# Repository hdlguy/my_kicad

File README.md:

#               my_kicad

This is a repo to contain some simple attempts to use Kicad 6 to design printed circuit boards.

## File organization and version control

I like to make it so that design files are usable by just cloning them from GitHub but that is not completely possible with KiCad because libraries are external to the design folders and KiCad relies on user level pathname to access libraries.

Here are how I have my paths setup.

The official KiCad libraries are cloned from these url:

    https://gitlab.com/kicad/libraries/kicad-symbols
    https://gitlab.com/kicad/libraries/kicad-footprints
    https://gitlab.com/kicad/libraries/kicad-packages3d

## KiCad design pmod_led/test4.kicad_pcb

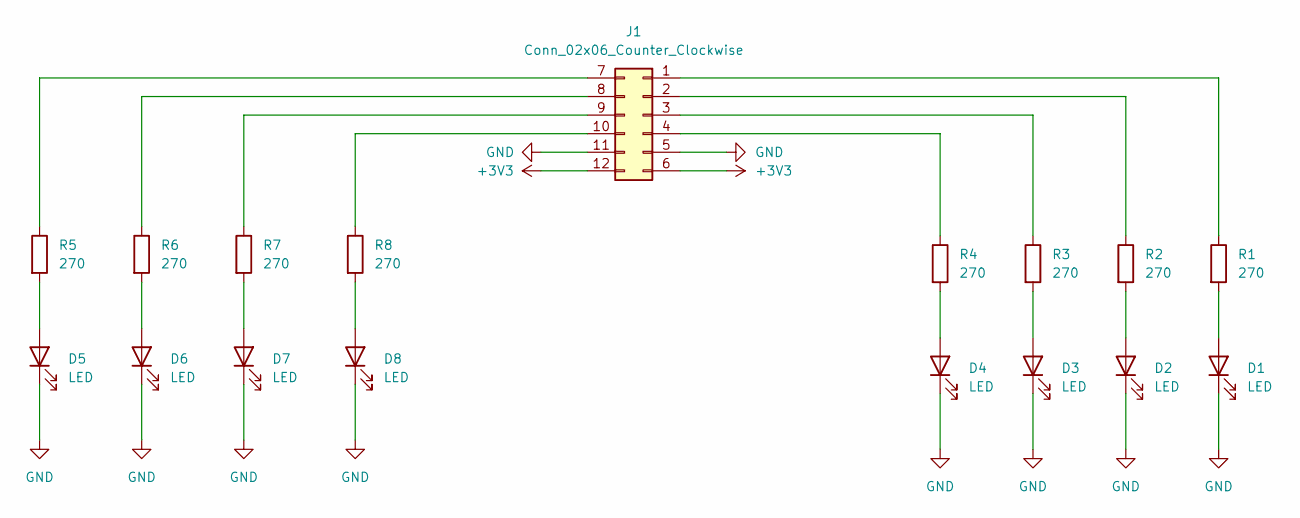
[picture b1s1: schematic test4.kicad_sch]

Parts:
D1, D2, D3, D4, D5, D6, D7, D8: LED; LED_0603_1608Metric
J1: Conn_02x06_Counter_Clockwise; PinHeader_2x06_P2.54mm_Horizontal
R1, R2, R3, R4, R5, R6, R7, R8: 270; R_0603_1608Metric

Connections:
+3V3: J1.6, J1.12
GND: D1.1 (K), D2.1 (K), D3.1 (K), D4.1 (K), D5.1 (K), D6.1 (K), D7.1 (K), D8.1 (K), J1.5, J1.11
unnamed: D6.2 (A), R6.2
unnamed: D7.2 (A), R7.2
unnamed: D8.2 (A), R8.2
unnamed: D4.2 (A), R4.2
unnamed: D3.2 (A), R3.2
unnamed: D2.2 (A), R2.2
unnamed: D1.2 (A), R1.2
unnamed: J1.1, R1.1
unnamed: J1.2, R2.1
unnamed: J1.3, R3.1
unnamed: J1.4, R4.1
unnamed: J1.8, R6.1
unnamed: J1.9, R7.1
unnamed: J1.10, R8.1
unnamed: J1.7, R5.1
unnamed: D5.2 (A), R5.2

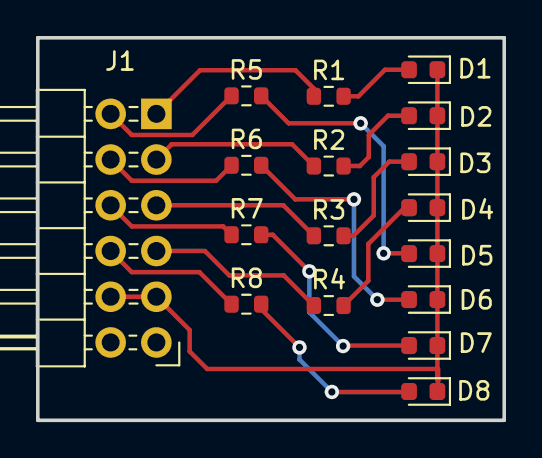
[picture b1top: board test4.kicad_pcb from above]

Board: 2 copper layers, 25.9 x 21.2 mm, 17 parts (0 on the bottom side), 18 nets.

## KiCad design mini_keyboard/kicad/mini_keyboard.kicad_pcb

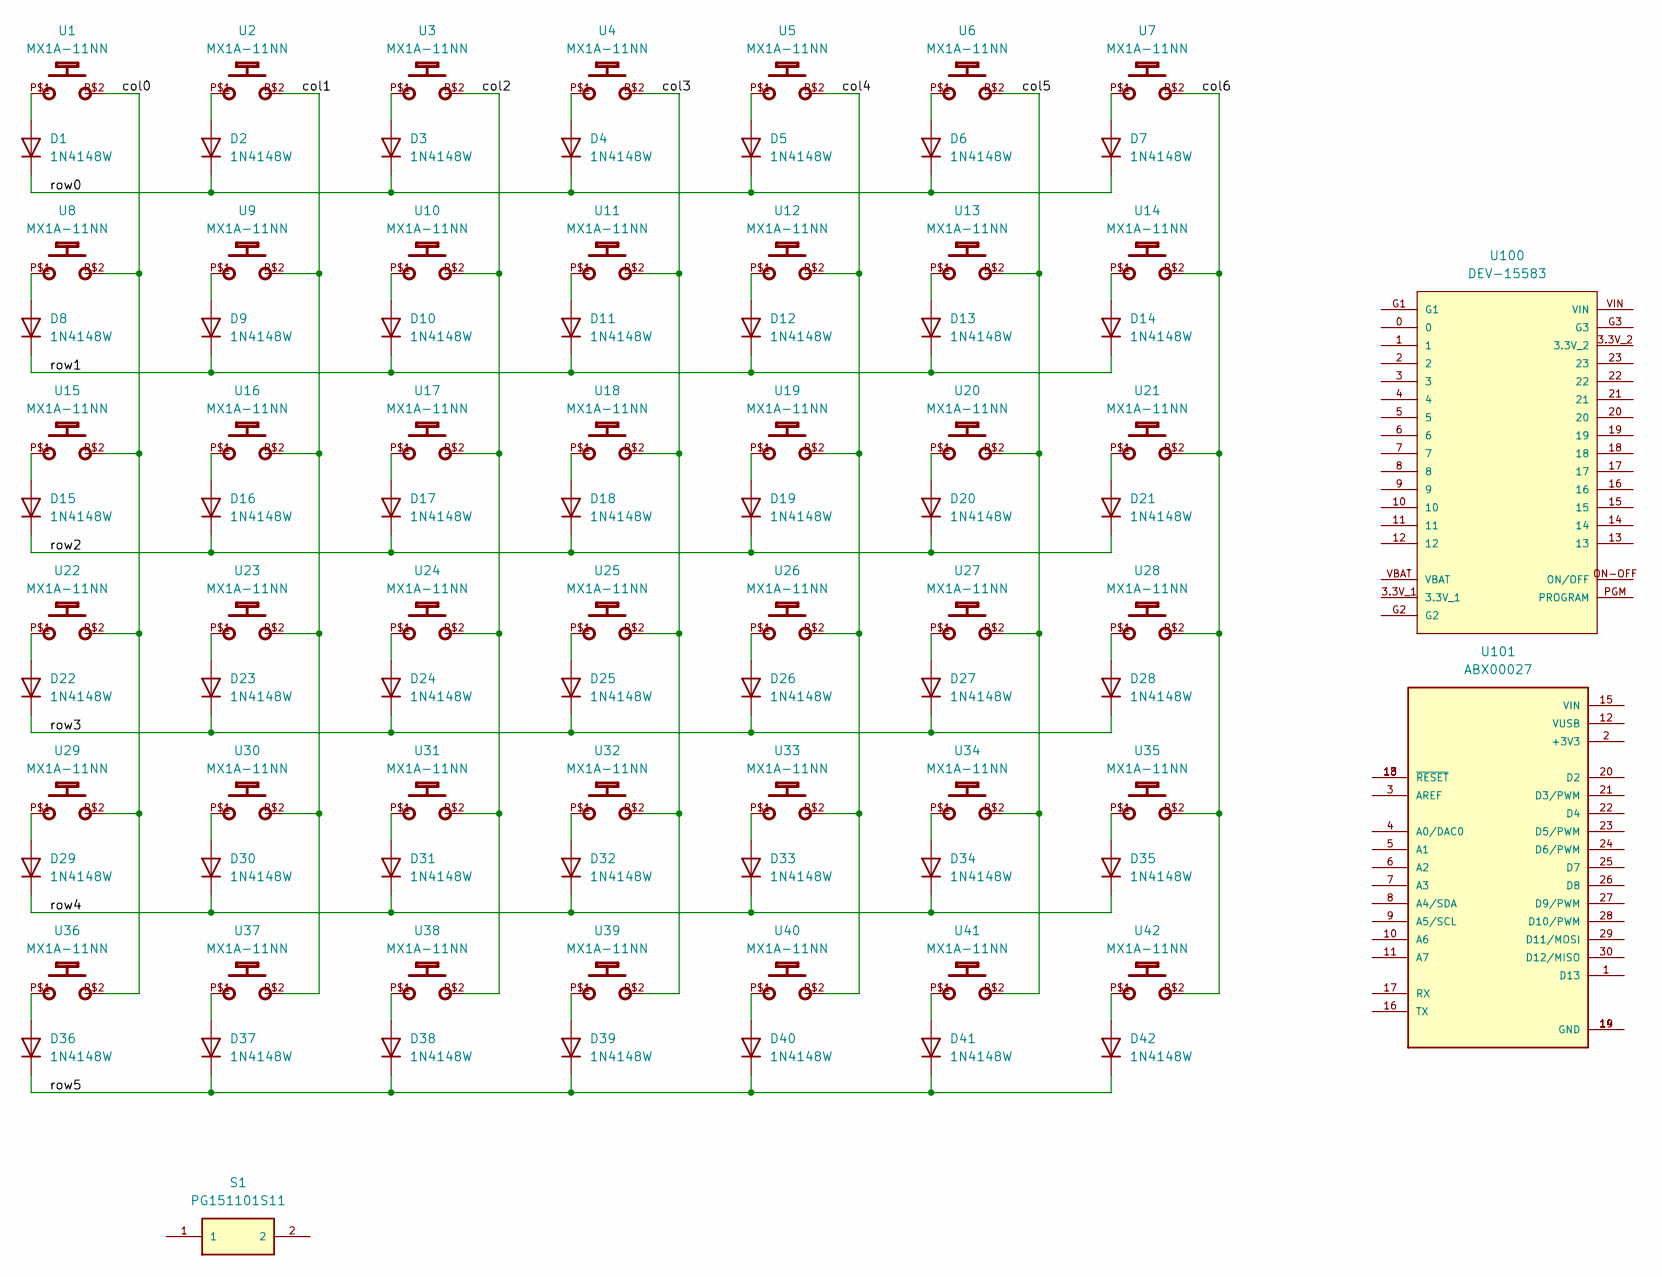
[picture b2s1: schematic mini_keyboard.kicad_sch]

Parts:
D1, D2, D3, D4, D5, D6, D7, D8, D9, D10, D11, D12, D13, D14, D15, D16, D17, D18, D19, D20, D21, D22, D23, D24, D25, D26, D27, D28, D29, D30, D31, D32, D33, D34, D35, D36, D37, D38, D39, D40, D41, D42: 1N4148W; D_SOD-123
S1: PG151101S11; SW_PG151101S11; PARTREV A
U1, U2, U3, U4, U5, U6, U7, U8, U9, U10, U11, U12, U13, U14, U15, U16, U17, U18, U19, U20, U21, U22, U23, U24, U25, U26, U27, U28, U29, U30, U31, U32, U33, U34, U35, U36, U37, U38, U39, U40, U41, U42: MX1A-11NN; CHERRY_MX1A-11NN_SWITCH
U100: DEV-15583; MODULE_DEV-15583
U101: ABX00027; MODULE_ABX00027

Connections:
/col0: U1.P$2, U8.P$2, U15.P$2, U22.P$2, U29.P$2, U36.P$2
/col1: U2.P$2, U9.P$2, U16.P$2, U23.P$2, U30.P$2, U37.P$2
/col2: U3.P$2, U10.P$2, U17.P$2, U24.P$2, U31.P$2, U38.P$2
/col3: U4.P$2, U11.P$2, U18.P$2, U25.P$2, U32.P$2, U39.P$2
/col4: U5.P$2, U12.P$2, U19.P$2, U26.P$2, U33.P$2, U40.P$2
/col5: U6.P$2, U13.P$2, U20.P$2, U27.P$2, U34.P$2, U41.P$2
/col6: U7.P$2, U14.P$2, U21.P$2, U28.P$2, U35.P$2, U42.P$2
/row0: D1.1 (K), D2.1 (K), D3.1 (K), D4.1 (K), D5.1 (K), D6.1 (K), D7.1 (K)
/row1: D8.1 (K), D9.1 (K), D10.1 (K), D11.1 (K), D12.1 (K), D13.1 (K), D14.1 (K)
/row2: D15.1 (K), D16.1 (K), D17.1 (K), D18.1 (K), D19.1 (K), D20.1 (K), D21.1 (K)
/row3: D22.1 (K), D23.1 (K), D24.1 (K), D25.1 (K), D26.1 (K), D27.1 (K), D28.1 (K)
/row4: D29.1 (K), D30.1 (K), D31.1 (K), D32.1 (K), D33.1 (K), D34.1 (K), D35.1 (K)
/row5: D36.1 (K), D37.1 (K), D38.1 (K), D39.1 (K), D40.1 (K), D41.1 (K), D42.1 (K)
unnamed: D1.2 (A), U1.P$1
unnamed: D2.2 (A), U2.P$1
unnamed: D3.2 (A), U3.P$1
unnamed: D4.2 (A), U4.P$1
unnamed: D5.2 (A), U5.P$1
unnamed: D6.2 (A), U6.P$1
unnamed: D7.2 (A), U7.P$1
unnamed: D8.2 (A), U8.P$1
unnamed: D9.2 (A), U9.P$1
unnamed: D10.2 (A), U10.P$1
unnamed: D11.2 (A), U11.P$1
unnamed: D12.2 (A), U12.P$1
unnamed: D13.2 (A), U13.P$1
unnamed: D14.2 (A), U14.P$1
unnamed: D15.2 (A), U15.P$1
unnamed: D16.2 (A), U16.P$1
unnamed: D17.2 (A), U17.P$1
unnamed: D18.2 (A), U18.P$1
unnamed: D19.2 (A), U19.P$1
unnamed: D20.2 (A), U20.P$1
unnamed: D21.2 (A), U21.P$1
unnamed: D22.2 (A), U22.P$1
unnamed: D23.2 (A), U23.P$1
unnamed: D24.2 (A), U24.P$1
unnamed: D25.2 (A), U25.P$1
unnamed: D26.2 (A), U26.P$1
unnamed: D27.2 (A), U27.P$1
unnamed: D28.2 (A), U28.P$1
unnamed: D29.2 (A), U29.P$1
unnamed: D30.2 (A), U30.P$1
unnamed: D31.2 (A), U31.P$1
unnamed: D32.2 (A), U32.P$1
unnamed: D33.2 (A), U33.P$1
unnamed: D34.2 (A), U34.P$1
unnamed: D35.2 (A), U35.P$1
unnamed: D36.2 (A), U36.P$1
unnamed: D37.2 (A), U37.P$1
unnamed: D38.2 (A), U38.P$1
unnamed: D39.2 (A), U39.P$1
unnamed: D40.2 (A), U40.P$1
unnamed: D41.2 (A), U41.P$1
unnamed: D42.2 (A), U42.P$1
unnamed: U101.14 (GND), U101.19 (GND)
unnamed: U101.13 (~RESET), U101.18 (~RESET)

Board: 2 copper layers, 87 parts (45 on the bottom side), 57 nets, no tracks yet.

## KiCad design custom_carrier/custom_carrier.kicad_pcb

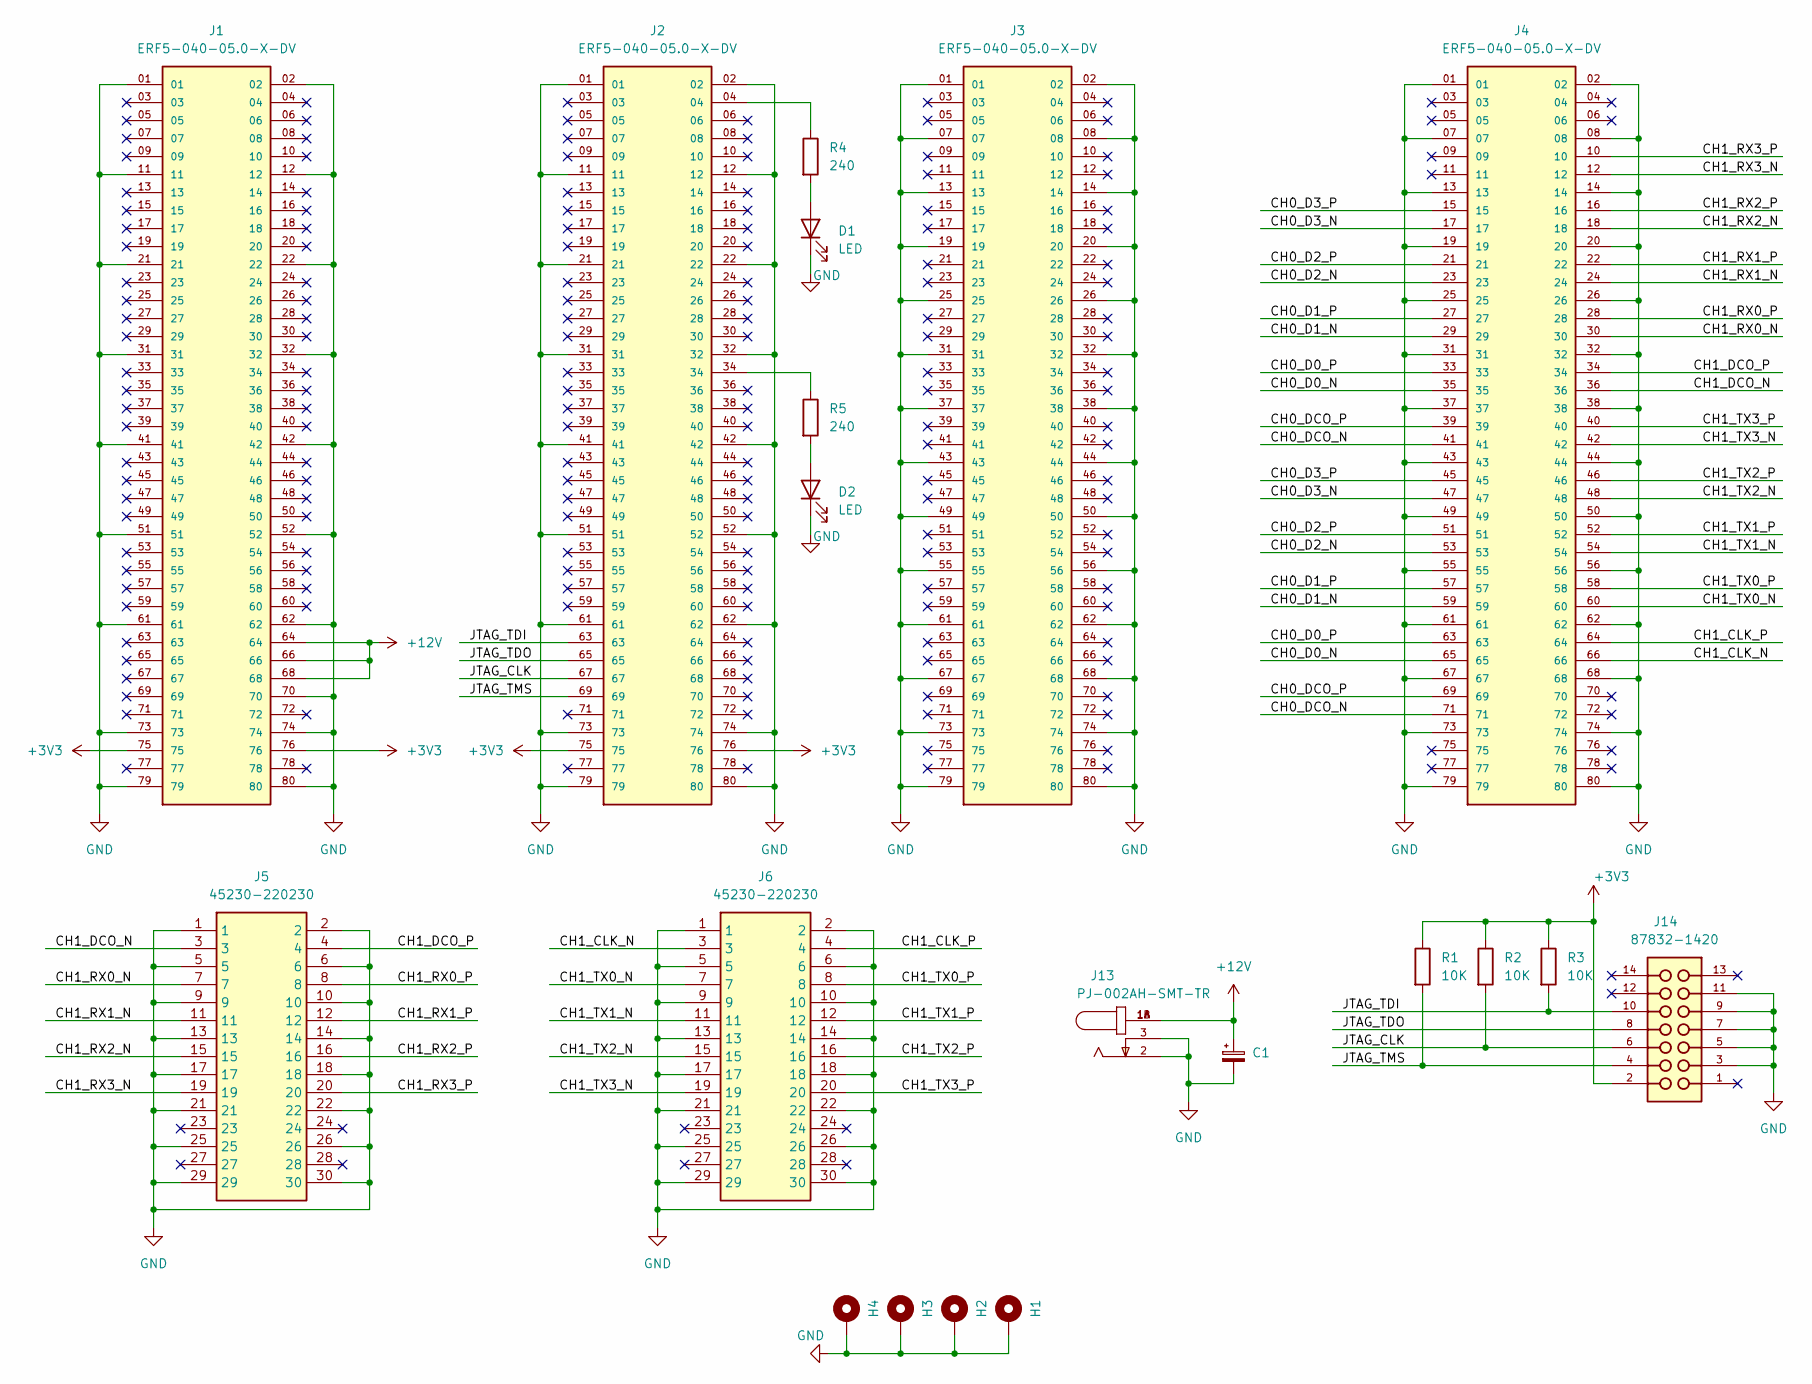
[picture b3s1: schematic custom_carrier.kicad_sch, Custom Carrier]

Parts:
C1: 22UF/25V; CP_EIA-3528-15_AVX-H; partnumber TCJB226M025R0150
D1, D2: LED; LED_0603_1608Metric
H1, H2, H3, H4: standoff_hole; MountingHole_2.2mm_M2_DIN965_Pad
J1, J2, J3, J4: ERF5-040-05.0-X-DV; SAMTEC_ERF5-040-05.0-X-DV; PARTREV F
J5, J6: 45230-220230; 45230220230; Manufacturer_Part_Number 45230-220230; Mouser Part Number 517-45230-220230
J13: PJ-002AH-SMT-TR; CUI_PJ-002AH-SMT-TR
J14: 87832-1420; MOLEX_87832-1420
R1, R2, R3: 10K; R_0603_1608Metric
R4, R5: 240; R_0603_1608Metric

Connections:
+3V3: J1.75, J1.76, J2.75, J2.76, J14.2, R1.1, R2.1, R3.1
+12V: C1.1, J1.64, J1.66, J1.68, J13.1A, J13.1B
/CH0_D0_N: J4.35, J4.65
/CH0_D0_P: J4.33, J4.63
/CH0_D1_N: J4.29, J4.59
/CH0_D1_P: J4.27, J4.57
/CH0_D2_N: J4.23, J4.53
/CH0_D2_P: J4.21, J4.51
/CH0_D3_N: J4.17, J4.47
/CH0_D3_P: J4.15, J4.45
/CH0_DCO_N: J4.41, J4.71
/CH0_DCO_P: J4.39, J4.69
/CH1_CLK_N: J4.66, J6.3
/CH1_CLK_P: J4.64, J6.4
/CH1_DCO_N: J4.36, J5.3
/CH1_DCO_P: J4.34, J5.4
/CH1_RX0_N: J4.30, J5.7
/CH1_RX0_P: J4.28, J5.8
/CH1_RX1_N: J4.24, J5.11
/CH1_RX1_P: J4.22, J5.12
/CH1_RX2_N: J4.18, J5.15
/CH1_RX2_P: J4.16, J5.16
/CH1_RX3_N: J4.12, J5.19
/CH1_RX3_P: J4.10, J5.20
/CH1_TX0_N: J4.60, J6.7
/CH1_TX0_P: J4.58, J6.8
/CH1_TX1_N: J4.54, J6.11
/CH1_TX1_P: J4.52, J6.12
/CH1_TX2_N: J4.48, J6.15
/CH1_TX2_P: J4.46, J6.16
/CH1_TX3_N: J4.42, J6.19
/CH1_TX3_P: J4.40, J6.20
/JTAG_CLK: J2.67, J14.6, R2.2
/JTAG_TDI: J2.63, J14.10, R3.2
/JTAG_TDO: J2.65, J14.8
/JTAG_TMS: J2.69, J14.4, R1.2
GND: C1.2, D1.1 (K), D2.1 (K), H1.1, H2.1, H3.1, H4.1, J1.01, J1.02, J1.11, J1.12, J1.21, J1.22, J1.31, J1.32, J1.41, J1.42, J1.51, J1.52, J1.61, J1.62, J1.70, J1.73, J1.74, J1.79, J1.80, J2.01, J2.02, J2.11, J2.12, J2.21, J2.22, J2.31, J2.32, J2.41, J2.42, J2.51, J2.52, J2.61, J2.62, J2.73, J2.74, J2.79, J2.80, J3.01, J3.02, J3.07, J3.08, J3.13, J3.14, J3.19, J3.20, J3.25, J3.26, J3.31, J3.32, J3.37, J3.38, J3.43, J3.44, J3.49, J3.50, J3.55, J3.56, J3.61, J3.62, J3.67, J3.68, J3.73, J3.74, J3.79, J3.80, J4.01, J4.02, J4.07, J4.08, J4.13, J4.14, J4.19, J4.20, J4.25, J4.26, J4.31, J4.32, J4.37, J4.38, J4.43, J4.44, J4.49, J4.50, J4.55, J4.56, J4.61, J4.62, J4.67, J4.68, J4.73, J4.74, J4.79, J4.80, J5.1, J5.2, J5.5, J5.6, J5.9, J5.10, J5.13, J5.14, J5.17, J5.18, J5.21, J5.22, J5.25, J5.26, J5.29, J5.30, J6.1, J6.2, J6.5, J6.6, J6.9, J6.10, J6.13, J6.14, J6.17, J6.18, J6.21, J6.22, J6.25, J6.26, J6.29, J6.30, J13.2, J13.3, J14.3, J14.5, J14.7, J14.9, J14.11
unnamed: D1.2 (A), R4.2
unnamed: D2.2 (A), R5.2
unnamed: J2.04, R4.1
unnamed: J2.34, R5.1

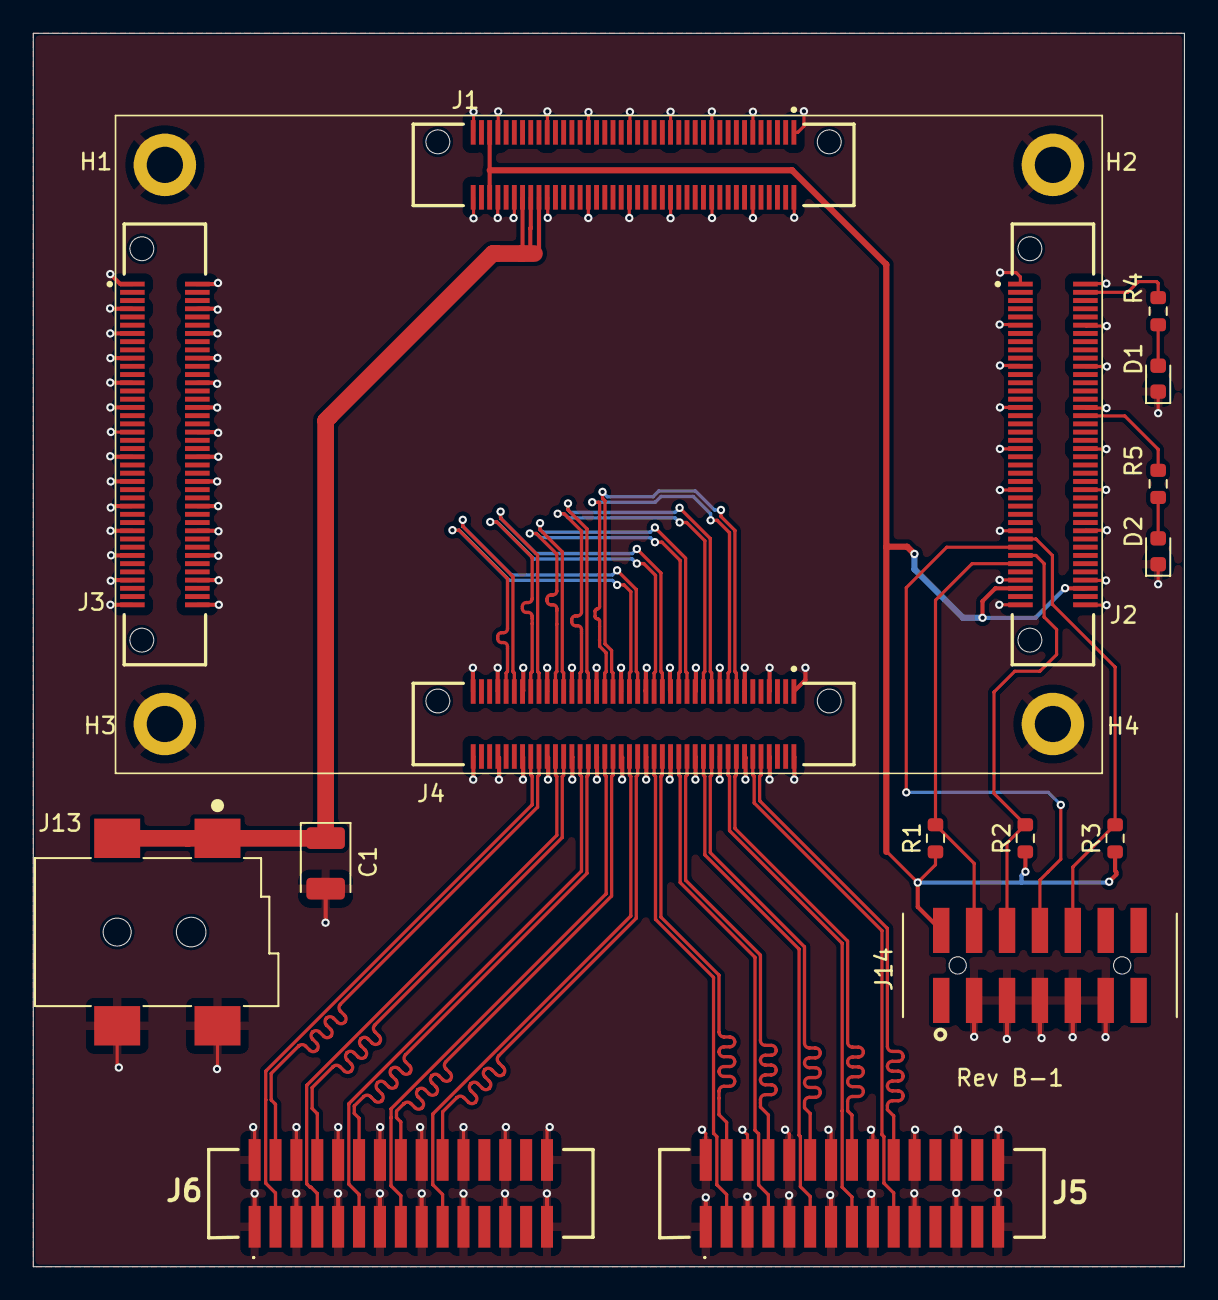
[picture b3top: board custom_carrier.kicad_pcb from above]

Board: 4 copper layers, 70.0 x 75.0 mm, 20 parts (0 on the bottom side), 41 nets.

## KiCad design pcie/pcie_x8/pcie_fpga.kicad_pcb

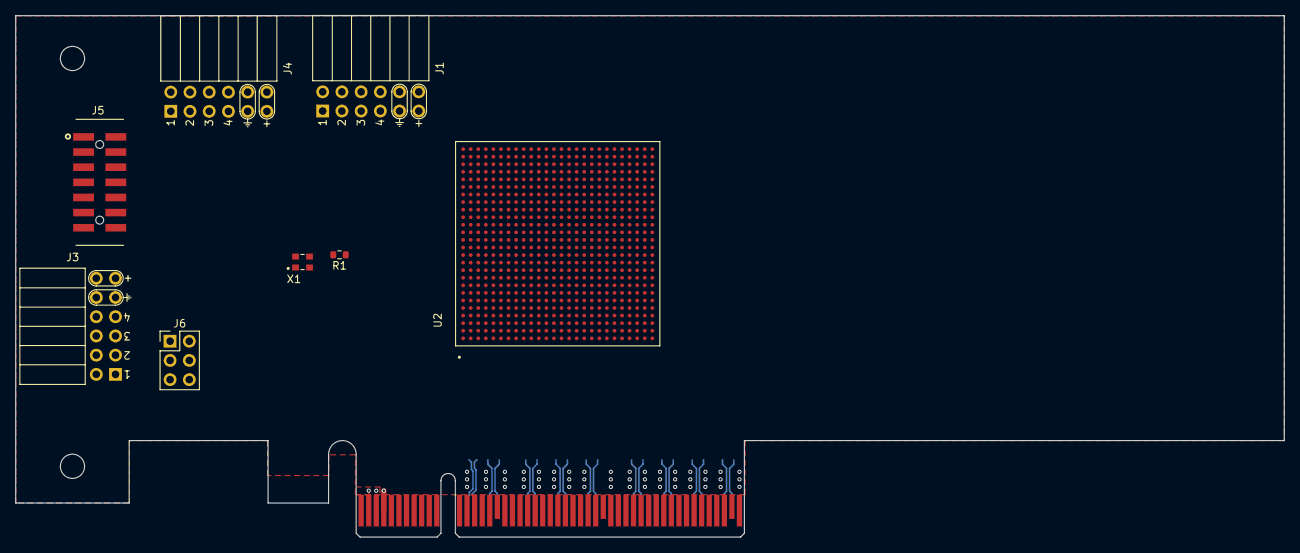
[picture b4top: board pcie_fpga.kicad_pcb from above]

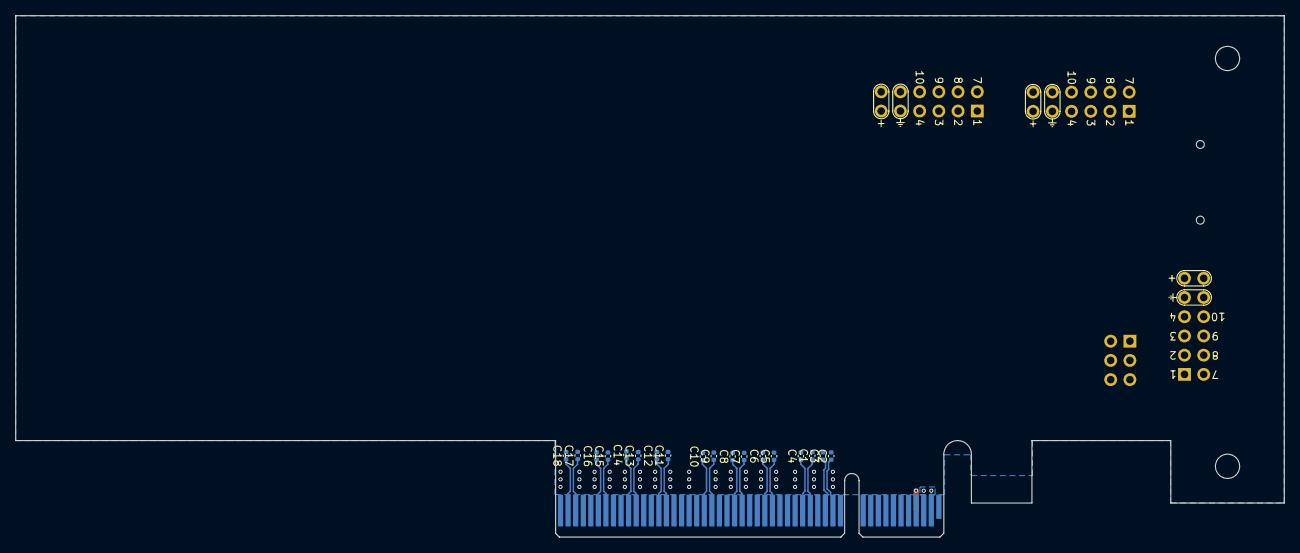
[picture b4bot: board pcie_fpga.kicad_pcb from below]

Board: 6 copper layers, 167.7 x 68.9 mm, 27 parts (18 on the bottom side), 77 nets.

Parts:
C1, C2, C3, C4, C5, C6, C7, C8, C9, C10, C11, C12, C13, C14, C15, C16, C17, C18: 0.01uf; C_0402_1005Metric
J1, J3, J4: PMOD_Host_Conn_02x06; PMOD_PinSocket_2x06_P2.54mm_Horizontal
J2: PCIexpress_x8
J5: 87832-1420; MOLEX_87832-1420
J6: Conn_02x03_Odd_Even; PinHeader_2x03_P2.54mm_Vertical
R1: 10; R_0603_1608Metric
U2: XCAU10P-1FFVB676I; IC_XCAU10P-1FFVB676I
X1: ECS-2520MVQ-1000-BN-TR; OSC_ECS-2520S25-250-FN-TR

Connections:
+3V3: J2.A9 (+3.3V), J2.A10 (+3.3V), J2.B8 (+3.3V), X1.4 (VDD)
+12V: J2.A2 (+12V), J2.A3 (+12V), J2.B1 (+12V), J2.B2 (+12V), J2.B3 (+12V)
/ac_refclk_N: C3.2, U2.V6 (MGTREFCLK0N_225)
/ac_refclk_P: C2.2, U2.V7 (MGTREFCLK0P_225)
/oscout: R1.2, X1.3 (OUT)
/per0_N: C4.1, J2.A17 (PERn0)
/per0_P: C1.1, J2.A16 (PERp0)
/per1_N: C6.1, J2.A22 (PERn1)
/per1_P: C5.1, J2.A21 (PERp1)
/per2_N: C8.1, J2.A26 (PERn2)
/per2_P: C7.1, J2.A25 (PERp2)
/per3_N: C10.1, J2.A30 (PERn3)
/per3_P: C9.1, J2.A29 (PERp3)
/per4_N: C12.1, J2.A36 (PERn4)
/per4_P: C11.1, J2.A35 (PERp4)
/per5_N: C14.1, J2.A40 (PERn5)
/per5_P: C13.1, J2.A39 (PERp5)
/per6_N: C16.1, J2.A44 (PERn6)
/per6_P: C15.1, J2.A43 (PERp6)
/per7_N: C18.1, J2.A48 (PERn7)
/per7_P: C17.1, J2.A47 (PERp7)
/pet0_N: J2.B15 (PETn0), U2.P1 (MGTHRXN3_225)
/pet0_P: J2.B14 (PETp0), U2.P2 (MGTHRXP3_225)
/pet1_N: J2.B20 (PETn1), U2.T1 (MGTHRXN2_225)
/pet1_P: J2.B19 (PETp1), U2.T2 (MGTHRXP2_225)
/pet2_N: J2.B24 (PETn2), U2.V1 (MGTHRXN1_225)
/pet2_P: J2.B23 (PETp2), U2.V2 (MGTHRXP1_225)
/pet3_N: J2.B28 (PETn3), U2.Y1 (MGTHRXN0_225)
/pet3_P: J2.B27 (PETp3), U2.Y2 (MGTHRXP0_225)
/pet4_N: J2.B34 (PETn4), U2.AB1 (MGTHRXN3_224)
/pet4_P: J2.B33 (PETp4), U2.AB2 (MGTHRXP3_224)
/pet5_N: J2.B38 (PETn5), U2.AD1 (MGTHRXN2_224)
/pet5_P: J2.B37 (PETp5), U2.AD2 (MGTHRXP2_224)
/pet6_N: J2.B42 (PETn6), U2.AE3 (MGTHRXN1_224)
/pet6_P: J2.B41 (PETp6), U2.AE4 (MGTHRXP1_224)
/pet7_N: J2.B46 (PETn7), U2.AF1 (MGTHRXN0_224)
/pet7_P: J2.B45 (PETp7), U2.AF2 (MGTHRXP0_224)
/pre_per0_N: C4.2, U2.R4 (MGTHTXN3_225)
/pre_per0_P: C1.2, U2.R5 (MGTHTXP3_225)
/pre_per1_N: C6.2, U2.U4 (MGTHTXN2_225)
/pre_per1_P: C5.2, U2.U5 (MGTHTXP2_225)
/pre_per2_N: C8.2, U2.W4 (MGTHTXN1_225)
/pre_per2_P: C7.2, U2.W5 (MGTHTXP1_225)
/pre_per3_N: C10.2, U2.AA4 (MGTHTXN0_225)
/pre_per3_P: C9.2, U2.AA5 (MGTHTXP0_225)
/pre_per4_N: C12.2, U2.AC4 (MGTHTXN3_224)
/pre_per4_P: C11.2, U2.AC5 (MGTHTXP3_224)
/pre_per5_N: C14.2, U2.AD6 (MGTHTXN2_224)
/pre_per5_P: C13.2, U2.AD7 (MGTHTXP2_224)
/pre_per6_N: C16.2, U2.AE8 (MGTHTXN1_224)
/pre_per6_P: C15.2, U2.AE9 (MGTHTXP1_224)
/pre_per7_N: C18.2, U2.AF6 (MGTHTXN0_224)
/pre_per7_P: C17.2, U2.AF7 (MGTHTXP0_224)
/prsnt_x1: J2.B17 (~PRSNT2), J6.1
/prsnt_x4: J2.B31 (~PRSNT2), J6.3
/prsnt_x8: J2.B48 (~PRSNT2), J6.5
/prsntn: J2.A1 (~PRSNT1), J6.2, J6.4, J6.6
/refclk_N: C3.1, J2.A14 (REFCLK-)
/refclk_P: C2.1, J2.A13 (REFCLK+)
GND: J2.A4 (GND), J2.A12 (GND), J2.A15 (GND), J2.A18 (GND), J2.A20 (GND), J2.A23 (GND), J2.A24 (GND), J2.A27 (GND), J2.A28 (GND), J2.A31 (GND), J2.A34 (GND), J2.A37 (GND), J2.A38 (GND), J2.A41 (GND), J2.A42 (GND), J2.A45 (GND), J2.A46 (GND), J2.A49 (GND), J2.B4 (GND), J2.B7 (GND), J2.B13 (GND), J2.B16 (GND), J2.B18 (GND), J2.B21 (GND), J2.B22 (GND), J2.B25 (GND), J2.B26 (GND), J2.B29 (GND), J2.B32 (GND), J2.B35 (GND), J2.B36 (GND), J2.B39 (GND), J2.B40 (GND), J2.B43 (GND), J2.B44 (GND), J2.B47 (GND), J2.B49 (GND), U2.A1 (GND_1), U2.A2 (GND_1), U2.A5 (GND_1), U2.A6 (GND_1), U2.A8 (GND_1), U2.A11 (GND_1), U2.A16 (GND_1), U2.A21 (GND_1), U2.A26 (GND_1), U2.AA1 (GND_1), U2.AA2 (GND_1), U2.AA3 (GND_1), U2.AA6 (GND_2), U2.AA8 (GND_2), U2.AA16 (GND_2), U2.AA26 (GND_2), U2.AB3 (GND_2), U2.AB4 (GND_2), U2.AB8 (GND_2), U2.AB13 (GND_2), U2.AB23 (GND_2), U2.AC1 (GND_2), U2.AC2 (GND_2), U2.AC3 (GND_2), U2.AC6 (GND_3), U2.AC8 (GND_3), U2.AC9 (GND_3), U2.AC10 (GND_3), U2.AC20 (GND_3), U2.AC25 (GND_3), U2.AD3 (GND_3), U2.AD4 (GND_3), U2.AD5 (GND_3), U2.AD10 (GND_3), U2.AD17 (GND_3), U2.AE1 (GND_3), U2.AE2 (GND_4), U2.AE5 (GND_4), U2.AE6 (GND_4), U2.AE10 (GND_4), U2.AE14 (GND_4), U2.AE19 (GND_4), U2.AE24 (GND_4), U2.AF3 (GND_4), U2.AF4 (GND_4), U2.AF5 (GND_4), U2.AF8 (GND_4), U2.AF9 (GND_4), U2.AF10 (GND_5), U2.AF11 (GND_5), U2.AF16 (GND_5), U2.AF21 (GND_5), U2.AF26 (GND_5), U2.B3 (GND_5), U2.B4 (GND_5), U2.B5 (GND_5), U2.B8 (GND_5), U2.B13 (GND_5), U2.B18 (GND_5), U2.B23 (GND_5), U2.C1 (GND_6), U2.C2 (GND_6), U2.C5 (GND_6), U2.C6 (GND_6), U2.C8 (GND_6), U2.C10 (GND_6), U2.C15 (GND_6), U2.C25 (GND_6), U2.D3 (GND_6), U2.D4 (GND_6), U2.D5 (GND_6), U2.D8 (GND_6), U2.D12 (GND_7), U2.D22 (GND_7), U2.E1 (GND_7), U2.E2 (GND_7), U2.E3 (GND_7), U2.E6 (GND_7), U2.E8 (GND_7), U2.E19 (GND_7), U2.F3 (GND_7), U2.F4 (GND_7), U2.F8 (GND_7), U2.F11 (GND_7), U2.F16 (GND_8), U2.F21 (GND_8), U2.F26 (GND_8), U2.G1 (GND_8), U2.G2 (GND_8), U2.G3 (GND_8), U2.G6 (GND_8), U2.G8 (GND_8), U2.G13 (GND_8), U2.G23 (GND_8), U2.H3 (GND_8), U2.H4 (GND_8), U2.H8 (GND_9), U2.H20 (GND_9), U2.J1 (GND_9), U2.J2 (GND_9), U2.J3 (GND_9), U2.J6 (GND_9), U2.J8 (GND_9), U2.J17 (GND_9), U2.K3 (GND_9), U2.K4 (GND_9), U2.K8 (GND_9), U2.K12 (GND_9), U2.K14 (GND_10), U2.K16 (GND_10), U2.K19 (GND_10), U2.K24 (GND_10), U2.L1 (GND_10), U2.L2 (GND_10), U2.L3 (GND_10), U2.L6 (GND_10), U2.L8 (GND_10), U2.L11 (GND_10), U2.L13 (GND_10), U2.L15 (GND_10), U2.L17 (GND_11), U2.L21 (GND_11), U2.L26 (GND_11), U2.M3 (GND_11), U2.M4 (GND_11), U2.M8 (GND_11), U2.M10 (GND_11), U2.M12 (GND_11), U2.M14 (GND_11), U2.M16 (GND_11), U2.M23 (GND_11), U2.N1 (GND_11), U2.N2 (GND_12), U2.N3 (GND_12), U2.N6 (GND_12), U2.N8 (GND_12), U2.N11 (GND_12), U2.N15 (GND_12), U2.N17 (GND_12), U2.N20 (GND_12), U2.N25 (GND_12), U2.P3 (GND_12), U2.P4 (GND_12), U2.P8 (GND_12), U2.P10 (GND_12), U2.P12 (GND_13), U2.P16 (GND_13), U2.R1 (GND_13), U2.R2 (GND_13), U2.R3 (GND_13), U2.R6 (GND_13), U2.R8 (GND_13), U2.R11 (GND_13), U2.R15 (GND_13), U2.R17 (GND_13), U2.R19 (GND_13), U2.R24 (GND_13), U2.T3 (GND_14), U2.T4 (GND_14), U2.T8 (GND_14), U2.T10 (GND_14), U2.T12 (GND_14), U2.T16 (GND_14), U2.T21 (GND_14), U2.T26 (GND_14), U2.U1 (GND_14), U2.U2 (GND_14), U2.U3 (GND_14), U2.U6 (GND_14), U2.U8 (GND_15), U2.U11 (GND_15), U2.U13 (GND_15), U2.U15 (GND_15), U2.U17 (GND_15), U2.U18 (GND_15), U2.V3 (GND_15), U2.V4 (GND_15), U2.V8 (GND_15), U2.V10 (GND_15), U2.V12 (GND_15), U2.V14 (GND_15), U2.V16 (GND_16), U2.V20 (GND_16), U2.V25 (GND_16), U2.W1 (GND_16), U2.W2 (GND_16), U2.W3 (GND_16), U2.W6 (GND_16), U2.W8 (GND_16), U2.W17 (GND_16), U2.W22 (GND_16), U2.Y3 (GND_16), U2.Y4 (GND_16), U2.Y8 (GND_16), U2.Y19 (GND_16), X1.2 (GND)
unnamed: U2.A7 (MGTAVTT_R), U2.AB5 (MGTAVTT_R), U2.AE7 (MGTAVTT_R), U2.C7 (MGTAVTT_R), U2.E7 (MGTAVTT_R), U2.F5 (MGTAVTT_R), U2.G7 (MGTAVTT_R), U2.H5 (MGTAVTT_R), U2.K5 (MGTAVTT_R), U2.M5 (MGTAVTT_R), U2.P5 (MGTAVTT_R), U2.T5 (MGTAVTT_R), U2.V5 (MGTAVTT_R), U2.Y5 (MGTAVTT_R)
unnamed: U2.AA7 (MGTAVCC_R), U2.AC7 (MGTAVCC_R), U2.J7 (MGTAVCC_R), U2.L7 (MGTAVCC_R), U2.N7 (MGTAVCC_R), U2.W7 (MGTAVCC_R)
unnamed: U2.AA11 (VCCO_0), U2.AD12 (VCCO_0)
unnamed: U2.AA21 (VCCO_64), U2.AB18 (VCCO_64), U2.AD22 (VCCO_64)
unnamed: U2.AC15 (VCCO_84), U2.Y14 (VCCO_84)
unnamed: U2.E9 (VCCO_85), U2.H10 (VCCO_85)
unnamed: U2.E14 (VCCO_86), U2.H15 (VCCO_86)
unnamed: U2.E24 (VCCO_66), U2.H25 (VCCO_66), U2.J22 (VCCO_66)
unnamed: U2.K11 (VCCINT_1), U2.K13 (VCCINT_1), U2.K15 (VCCINT_1), U2.K17 (VCCINT_1), U2.L10 (VCCINT_1), U2.L12 (VCCINT_1), U2.L14 (VCCINT_1), U2.L16 (VCCINT_1), U2.M11 (VCCINT_1), U2.M13 (VCCINT_1)
unnamed: U2.L9 (VCCINT_IO), U2.M9 (VCCINT_IO), U2.N9 (VCCINT_IO), U2.P9 (VCCINT_IO)
unnamed: U2.M15 (VCCINT_2), U2.M17 (VCCINT_2), U2.N10 (VCCINT_2), U2.N12 (VCCINT_2), U2.N16 (VCCINT_2), U2.P11 (VCCINT_2), U2.P15 (VCCINT_2), U2.P17 (VCCINT_2), U2.R10 (VCCINT_2), U2.R12 (VCCINT_2), U2.R16 (VCCINT_2)
unnamed: U2.M18 (VCCAUX), U2.N18 (VCCAUX)
unnamed: U2.P18 (VCCAUX_IO), U2.R18 (VCCAUX_IO), U2.T18 (VCCAUX_IO)
unnamed: U2.P22 (VCCO_65), U2.U23 (VCCO_65), U2.Y24 (VCCO_65)
unnamed: U2.R7 (MGTVCCAUX_R), U2.U7 (MGTVCCAUX_R)
unnamed: U2.R9 (VCCBRAM), U2.T9 (VCCBRAM), U2.U9 (VCCBRAM), U2.V9 (VCCBRAM)
unnamed: U2.T11 (VCCINT_3), U2.T15 (VCCINT_3), U2.T17 (VCCINT_3), U2.U10 (VCCINT_3), U2.U12 (VCCINT_3), U2.U14 (VCCINT_3), U2.U16 (VCCINT_3), U2.V11 (VCCINT_3), U2.V13 (VCCINT_3), U2.V15 (VCCINT_3), U2.V17 (VCCINT_3)

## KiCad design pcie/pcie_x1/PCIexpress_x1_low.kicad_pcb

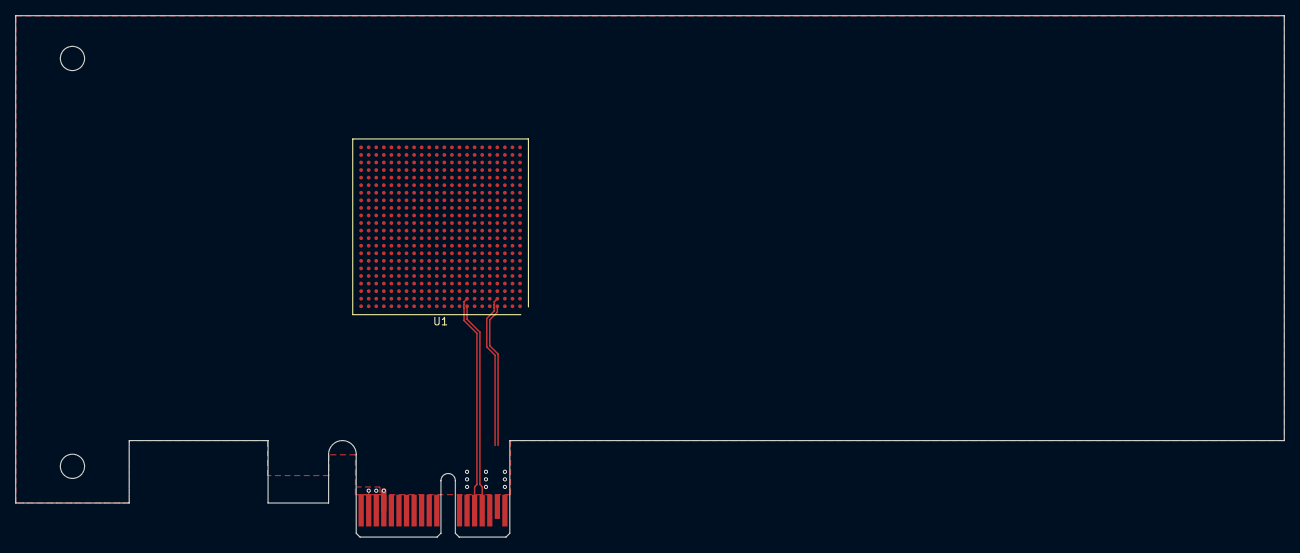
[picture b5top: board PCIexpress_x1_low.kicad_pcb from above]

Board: 4 copper layers, 167.7 x 68.9 mm, 5 parts (0 on the bottom side), 5 nets.

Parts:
J1, J2, J3: PCIexpress_bracket; PCIexpress_bracket_low
J1#2: PCIexpress_x1
U1: XC7A50T-FGG484; Xilinx_FGG484

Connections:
+3V3: J1#2.A9 (+3.3V), J1#2.A10 (+3.3V), J1#2.B8 (+3.3V)
+12V: J1#2.A2 (+12V), J1#2.A3 (+12V), J1#2.B1 (+12V), J1#2.B2 (+12V), J1#2.B3 (+12V)
/pet0_N: J1#2.B15 (PETn0), U1.A8 (MGTPRXN0_216)
/pet0_P: J1#2.B14 (PETp0), U1.B8 (MGTPRXP0_216)
GND: J1#2.A4 (GND), J1#2.A12 (GND), J1#2.A15 (GND), J1#2.A18 (GND), J1#2.B4 (GND), J1#2.B7 (GND), J1#2.B13 (GND), J1#2.B16 (GND), J1#2.B18 (GND)

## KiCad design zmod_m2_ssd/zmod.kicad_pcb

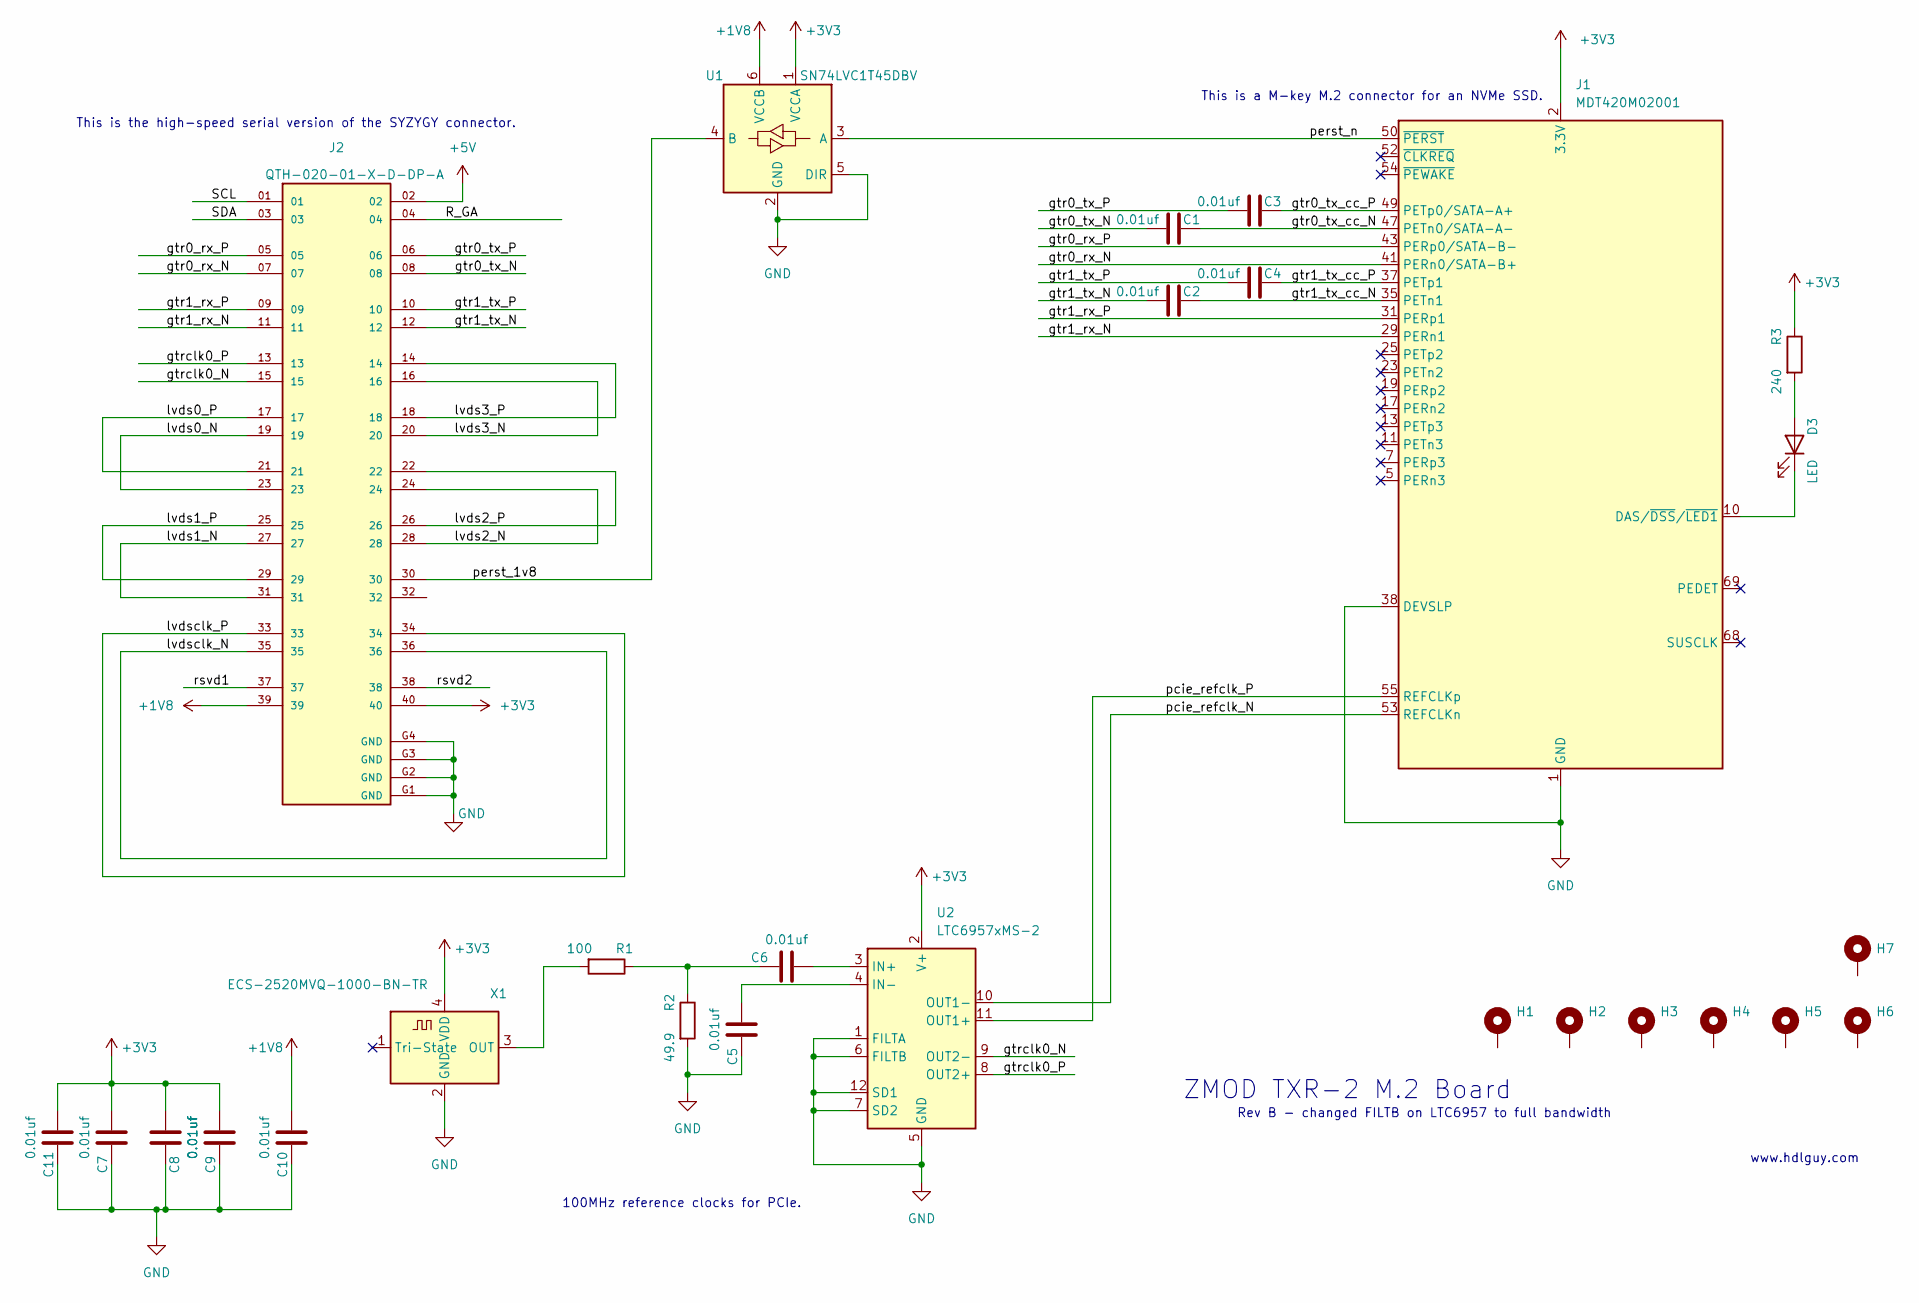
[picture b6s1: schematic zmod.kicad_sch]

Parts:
C1, C2, C3, C4, C5, C6, C7, C8, C9, C10, C11: 0.01uf; C_0603_1608Metric
D3: LED; LED_0603_1608Metric
H1, H2, H3, H4, H5, H6: MountingHole_Pad; MountingHole_3.2mm_M3_DIN965_Pad_TopBottom
H7: MountingHole_Pad; MountingHole_2.5mm_Pad
J1: MDT420M02001; TE_1-2199230-5
J2: QTH-020-01-X-D-DP-A; SAMTEC_QTH-020-01-X-D-DP-A; PARTREV L
R1: 100; R_0603_1608Metric
R2: 49.9; R_0603_1608Metric
R3: 240; R_0603_1608Metric
U1: SN74LVC1T45DBV; SOT-23-6
U2: LTC6957xMS-2; MSOP-12_3x4mm_P0.65mm
X1: ECS-2520MVQ-1000-BN-TR; OSC_ECS-2520S25-250-FN-TR

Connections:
+1V8: C10.2, J2.39, U1.6 (VCCB)
+3V3: C7.2, C8.2, C9.2, C11.2, J1.2 (3.3V), J1.4 (3.3V), J1.12 (3.3V), J1.14 (3.3V), J1.16 (3.3V), J1.18 (3.3V), J1.70 (3.3V), J1.72 (3.3V), J1.74 (3.3V), J2.40, R3.1, U1.1 (VCCA), U2.2 (V+), X1.4 (VDD)
+5V: J2.02
/R_GA: J2.04
/SCL: J2.01
/SDA: J2.03
/gtr0_rx_N: J1.41 (PERn0/SATA-B+), J2.07
/gtr0_rx_P: J1.43 (PERp0/SATA-B-), J2.05
/gtr0_tx_N: C1.1, J2.08
/gtr0_tx_P: C3.1, J2.06
/gtr0_tx_cc_N: C1.2, J1.47 (PETn0/SATA-A-)
/gtr0_tx_cc_P: C3.2, J1.49 (PETp0/SATA-A+)
/gtr1_rx_N: J1.29 (PERn1), J2.11
/gtr1_rx_P: J1.31 (PERp1), J2.09
/gtr1_tx_N: C2.1, J2.12
/gtr1_tx_P: C4.1, J2.10
/gtr1_tx_cc_N: C2.2, J1.35 (PETn1)
/gtr1_tx_cc_P: C4.2, J1.37 (PETp1)
/gtrclk0_N: J2.15, U2.9 (OUT2-)
/gtrclk0_P: J2.13, U2.8 (OUT2+)
/lvds0_N: J2.19, J2.23
/lvds0_P: J2.17, J2.21
/lvds1_N: J2.27, J2.31
/lvds1_P: J2.25, J2.29
/lvds2_N: J2.24, J2.28
/lvds2_P: J2.22, J2.26
/lvds3_N: J2.16, J2.20
/lvds3_P: J2.14, J2.18
/lvdsclk_N: J2.35, J2.36
/lvdsclk_P: J2.33, J2.34
/pcie_refclk_N: J1.53 (REFCLKn), U2.10 (OUT1-)
/pcie_refclk_P: J1.55 (REFCLKp), U2.11 (OUT1+)
/perst_1v8: J2.30, U1.4 (B)
/perst_n: J1.50 (~PERST), U1.3 (A)
/rsvd1: J2.37
/rsvd2: J2.38
GND: C5.1, C7.1, C8.1, C9.1, C10.1, C11.1, J1.1 (GND), J1.3 (GND), J1.9 (GND), J1.15 (GND), J1.21 (GND), J1.27 (GND), J1.33 (GND), J1.38 (DEVSLP), J1.39 (GND), J1.45 (GND), J1.51 (GND), J1.57 (GND), J1.71 (GND), J1.73 (GND), J1.75 (GND), J2.G1 (GND), J2.G2 (GND), J2.G3 (GND), J2.G4 (GND), R2.2, U1.2 (GND), U1.5 (DIR), U2.1 (FILTA), U2.5 (GND), U2.6 (FILTB), U2.7 (SD2), U2.12 (SD1), X1.2 (GND)
unnamed: C5.2, U2.4 (IN-)
unnamed: C6.1, R1.1, R2.1
unnamed: C6.2, U2.3 (IN+)
unnamed: D3.1 (K), J1.10 (DAS/~DSS/~LED1)
unnamed: D3.2 (A), R3.2
unnamed: R1.2, X1.3 (OUT)

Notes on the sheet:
100MHz reference clocks for PCIe.
www.hdlguy.com
This is the high-speed serial version of the SYZYGY connector.
This is a M-key M.2 connector for an NVMe SSD.
Rev B - changed FILTB on LTC6957 to full bandwidth
ZMOD TXR-2 M.2 Board
